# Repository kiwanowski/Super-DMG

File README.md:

# Super-DMG
a consolized Game Boy
## Features
* it has an HDMI port - [based on GbHdmi by Martoni](https://github.com/Martoni/GbHdmi)
* it lets you connect various bluetooth controllers - [based on BlueRetro by darthcloud](https://github.com/darthcloud/BlueRetro)

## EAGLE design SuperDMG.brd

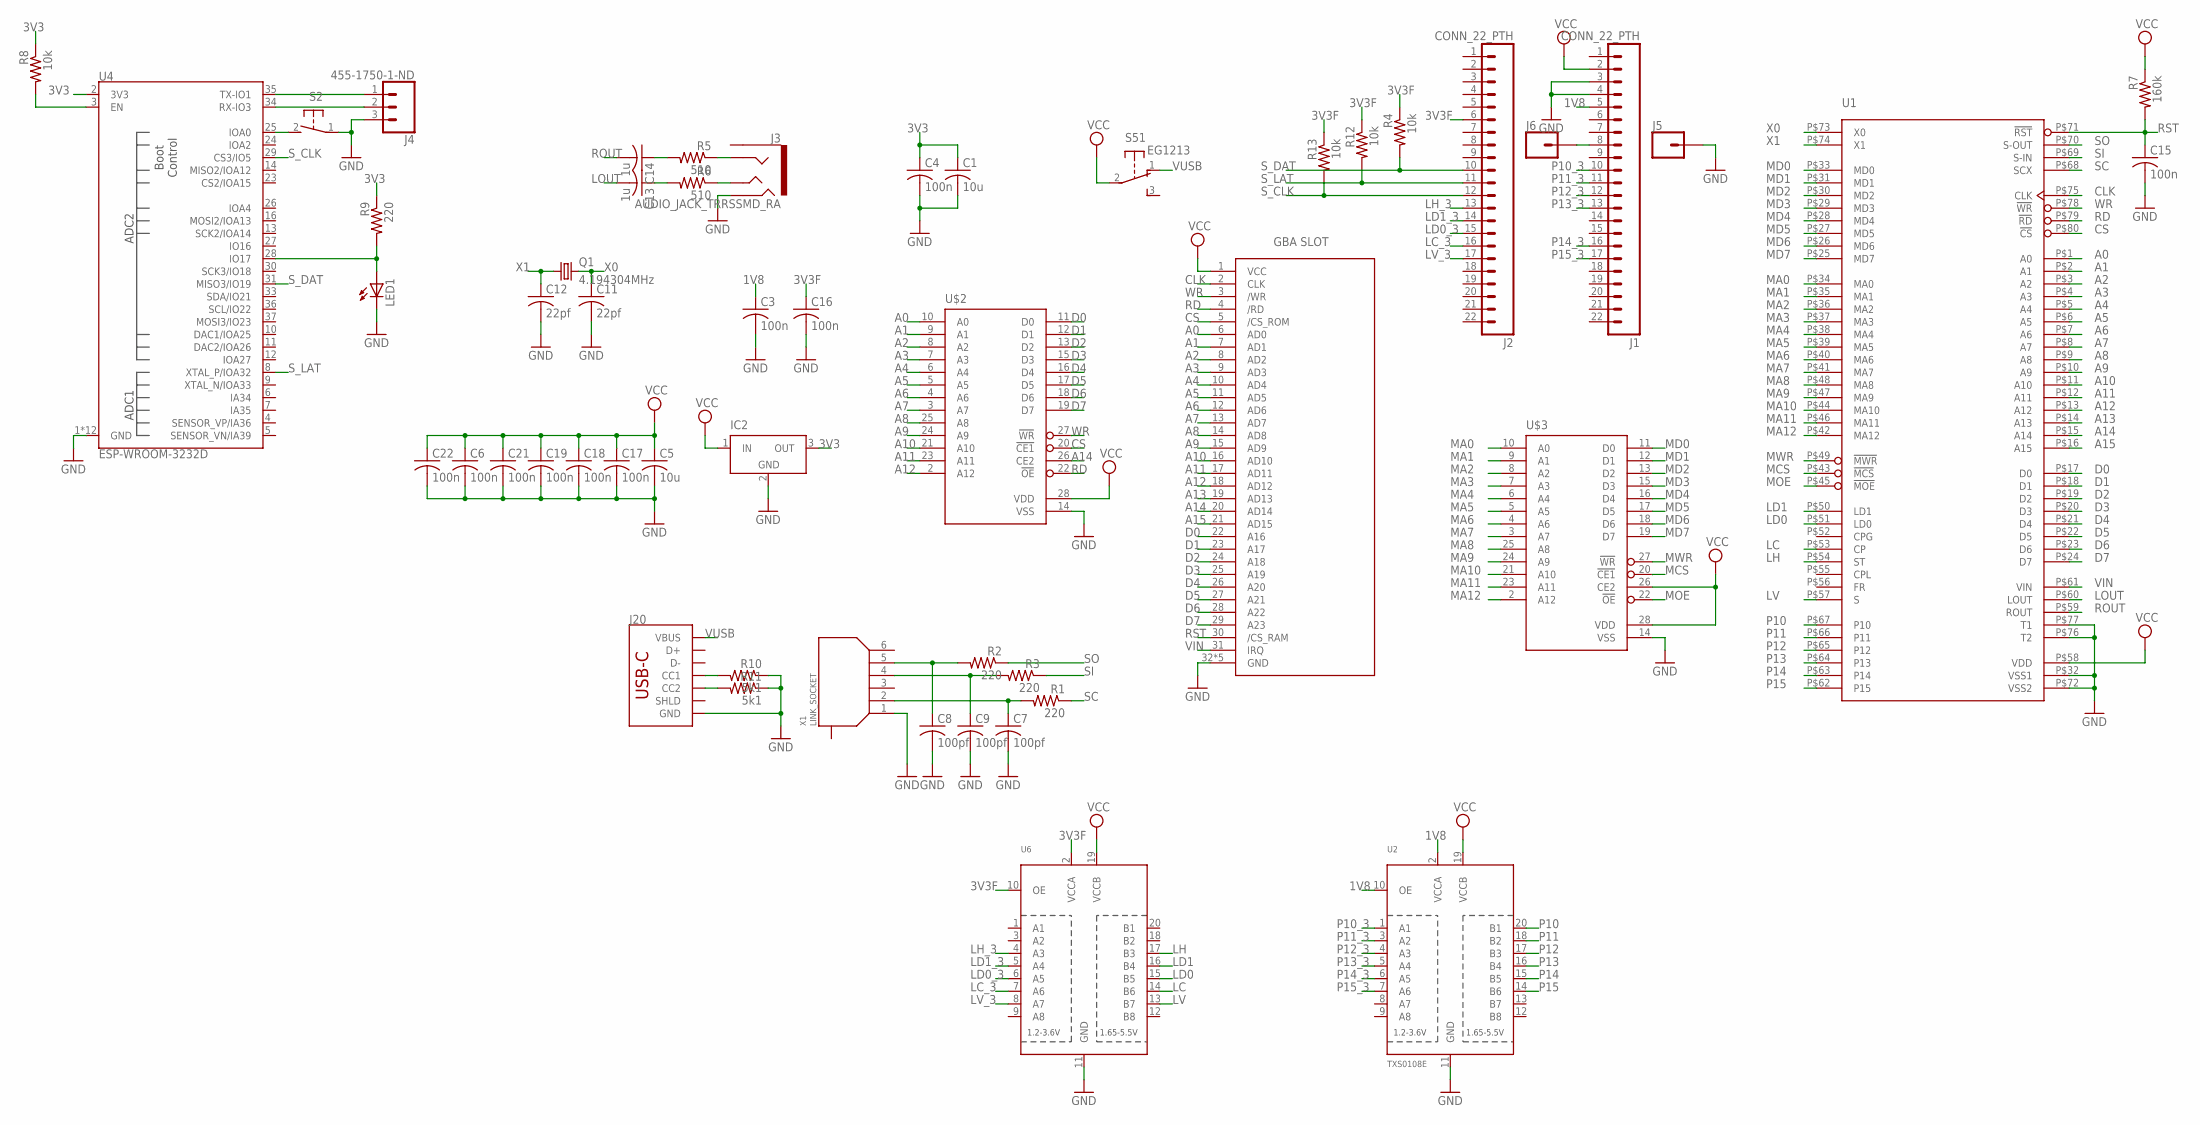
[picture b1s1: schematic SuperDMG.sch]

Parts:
C1, C5: 10u; C0805
C3, C4, C6, C15, C16, C17, C18, C19, C21, C22: 100n; C0805
C7, C8, C9: 100pf; C0805
C11, C12: 22pf; C0805
C13, C14: 1u; C0805
IC2: LT1129CST5; SOT223
J1, J2: CONN_22_PTH; 1X22
J3: AUDIO_JACK_TRRSSMD_RA; AUDIO_JACK_3.5MM_TRRS_SMD_RA
J4: 455-1750-1-ND; 1X03
J5, J6: CONN_01; 1X01
J20: USB_C_2-LAYER_PADS; USB-C-16P-2LAYER-PADS
LED1: LEDCHIP-LED0805; CHIP-LED0805
Q1: 4.194304MHz; HC49U-V
R1, R2, R3, R9: 220; R0805
R4, R8, R12, R13: 10k; R0805
R5, R6: 510; R0805
R7: 160k; R0805
R10, R11: 5k1; R0805
S2: 31-XX; B3F-31XX
S5: EG1213
U1: CPU-1GDMG; CPU-1G
U2: TXS0108E; TSSOP20
U4: ESP-WROOM-3232D; ESP-WROOM-32D
U6: TXB0108PWR; TSSOP20
U$1: GBA-SLOTSMD; GBA-SLOT
U$2, U$3: LH5264; SO28
X1: LINK_SOCKET

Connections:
1V8: C3.1, J1.5, U2.2 (VCCA), U2.10 (OE)
3V3: C1.1, C4.1, IC2.3 (OUT), R8.1, R9.1, U4.2 (3V3)
3V3F: C16.1, J2.6, R4.1, R12.1, R13.1, U6.2 (VCCA), U6.10 (OE)
A0: U1.P$1 (A0), U$1.6 (AD0), U$2.10 (A0)
A1: U1.P$2 (A1), U$1.7 (AD1), U$2.9 (A1)
A2: U1.P$3 (A2), U$1.8 (AD2), U$2.8 (A2)
A3: U1.P$4 (A3), U$1.9 (AD3), U$2.7 (A3)
A4: U1.P$5 (A4), U$1.10 (AD4), U$2.6 (A4)
A5: U1.P$6 (A5), U$1.11 (AD5), U$2.5 (A5)
A6: U1.P$7 (A6), U$1.12 (AD6), U$2.4 (A6)
A7: U1.P$8 (A7), U$1.13 (AD7), U$2.3 (A7)
A8: U1.P$9 (A8), U$1.14 (AD8), U$2.25 (A8)
A9: U1.P$10 (A9), U$1.15 (AD9), U$2.24 (A9)
A10: U1.P$11 (A10), U$1.16 (AD10), U$2.21 (A10)
A11: U1.P$12 (A11), U$1.17 (AD11), U$2.23 (A11)
A12: U1.P$13 (A12), U$1.18 (AD12), U$2.2 (A12)
A13: U1.P$14 (A13), U$1.19 (AD13)
A14: U1.P$15 (A14), U$1.20 (AD14), U$2.26 (CE2)
A15: U1.P$16 (A15), U$1.21 (AD15)
CLK: U1.P$75 (CLK), U$1.2 (CLK)
CS: U1.P$80 (!CS), U$1.5 (/CS_ROM), U$2.20 (!CE1)
D0: U1.P$17 (D0), U$1.22 (A16), U$2.11 (D0)
D1: U1.P$18 (D1), U$1.23 (A17), U$2.12 (D1)
D2: U1.P$19 (D2), U$1.24 (A18), U$2.13 (D2)
D3: U1.P$20 (D3), U$1.25 (A19), U$2.15 (D3)
D4: U1.P$21 (D4), U$1.26 (A20), U$2.16 (D4)
D5: U1.P$22 (D5), U$1.27 (A21), U$2.17 (D5)
D6: U1.P$23 (D6), U$1.28 (A22), U$2.18 (D6)
D7: U1.P$24 (D7), U$1.29 (A23), U$2.19 (D7)
GND: C1.2, C3.2, C4.2, C5.2, C6.2, C7.2, C8.2, C9.2, C11.2, C12.2, C15.2, C16.2, C17.2, C18.2, C19.2, C21.2, C22.2, IC2.2 (GND), IC2.4 (GND), J1.3, J1.4, J3.RING2, J4.3, J5.1, J20.GND, J20.GND2 (GND), LED1.C, R10.1, R11.1, S2.1, U1.P$32 (VSS1), U1.P$72 (VSS2), U1.P$76 (T2), U1.P$77 (T1), U2.11 (GND), U4.1 (GND), U4.15 (GND), U4.38 (GND), U4.GND, U4.GNDT1 (GND), U4.GNDT2 (GND), U4.GNDT3 (GND), U4.GNDT4 (GND), U4.GNDT5 (GND), U4.GNDT6 (GND), U4.GNDT7 (GND), U4.GNDT8 (GND), U6.11 (GND), U$1.32 (GND), U$1.SHIELD_1 (GND), U$1.SHIELD_2 (GND), U$1.SHIELD_3 (GND), U$1.SHIELD_4 (GND), U$2.14 (VSS), U$3.14 (VSS), X1.1
LC: U1.P$53 (CP), U6.14 (B6)
LC_3: J2.16, U6.7 (A6)
LD0: U1.P$51 (LD0), U6.15 (B5)
LD0_3: J2.15, U6.6 (A5)
LD1: U1.P$50 (LD1), U6.16 (B4)
LD1_3: J2.14, U6.5 (A4)
LH: U1.P$54 (ST), U6.17 (B3)
LH_3: J2.13, U6.4 (A3)
LOUT: C13.2, U1.P$60 (LOUT)
LV: U1.P$57 (S), U6.13 (B7)
LV_3: J2.17, U6.8 (A7)
MA0: U1.P$34 (MA0), U$3.10 (A0)
MA1: U1.P$35 (MA1), U$3.9 (A1)
MA2: U1.P$36 (MA2), U$3.8 (A2)
MA3: U1.P$37 (MA3), U$3.7 (A3)
MA4: U1.P$38 (MA4), U$3.6 (A4)
MA5: U1.P$39 (MA5), U$3.5 (A5)
MA6: U1.P$40 (MA6), U$3.4 (A6)
MA7: U1.P$41 (MA7), U$3.3 (A7)
MA8: U1.P$48 (MA8), U$3.25 (A8)
MA9: U1.P$47 (MA9), U$3.24 (A9)
MA10: U1.P$44 (MA10), U$3.21 (A10)
MA11: U1.P$46 (MA11), U$3.23 (A11)
MA12: U1.P$42 (MA12), U$3.2 (A12)
MCS: U1.P$43 (!MCS), U$3.20 (!CE1)
MD0: U1.P$33 (MD0), U$3.11 (D0)
MD1: U1.P$31 (MD1), U$3.12 (D1)
MD2: U1.P$30 (MD2), U$3.13 (D2)
MD3: U1.P$29 (MD3), U$3.15 (D3)
MD4: U1.P$28 (MD4), U$3.16 (D4)
MD5: U1.P$27 (MD5), U$3.17 (D5)
MD6: U1.P$26 (MD6), U$3.18 (D6)
MD7: U1.P$25 (MD7), U$3.19 (D7)
MOE: U1.P$45 (!MOE), U$3.22 (!OE)
MWR: U1.P$49 (!MWR), U$3.27 (!WR)
unnamed: C8.1, R2.2, X1.5
unnamed: C9.1, R3.2, X1.4
unnamed: J1.8, J6.1
unnamed: C7.1, R1.2, X1.2
unnamed: R8.2, U4.3 (EN)
unnamed: LED1.A, R9.2, U4.28 (IO17)
unnamed: J3.RING1, R5.1
unnamed: J20.A5 (CC1), R10.2
unnamed: J20.B5 (CC2), R11.2
unnamed: J3.TIP, R6.1
unnamed: C14.1, R5.2
unnamed: C13.1, R6.2
unnamed: S2.2 (S), U4.25 (IOA0)
P10: U1.P$67 (P10), U2.20 (B1)
P10_3: J1.10, U2.1 (A1)
P11: U1.P$66 (P11), U2.18 (B2)
P11_3: J1.11, U2.3 (A2)
P12: U1.P$65 (P12), U2.17 (B3)
P12_3: J1.12, U2.4 (A3)
P13: U1.P$64 (P13), U2.16 (B4)
P13_3: J1.13, U2.5 (A4)
P14: U1.P$63 (P14), U2.15 (B5)
P14_3: J1.16, U2.6 (A5)
P15: U1.P$62 (P15), U2.14 (B6)
P15_3: J1.17, U2.7 (A6)
RD: U1.P$79 (!RD), U$1.4 (/RD), U$2.22 (!OE)
ROUT: C14.2, U1.P$59 (ROUT)
RST: C15.1, R7.2, U1.P$71 (!RST), U$1.30 (/CS_RAM)
RX: J4.2, U4.34 (RX-IO3)
SC: R1.1, U1.P$68 (SCX)
SI: R3.1, U1.P$69 (S-IN)
SO: R2.1, U1.P$70 (S-OUT)
S_CLK: J2.12, R13.2, U4.29 (CS3/IO5)
S_DAT: J2.10, R4.2, U4.31 (MISO3/IO19)
S_LAT: J2.11, R12.2, U4.8 (XTAL_P/IOA32)
TX: J4.1, U4.35 (TX-IO1)
VCC: C5.1, C6.1, C17.1, C18.1, C19.1, C21.1, C22.1, IC2.1 (IN), J1.2, R7.1, S5.2, U1.P$58 (VDD), U2.19 (VCCB), U6.19 (VCCB), U$1.1 (VCC), U$2.28 (VDD), U$3.26 (CE2), U$3.28 (VDD)
VIN: U1.P$61 (VIN), U$1.31 (IRQ)
VUSB: J20.VBUS1 (VBUS), J20.VBUS2 (VBUS), S5.1 (O)
WR: U1.P$78 (!WR), U$1.3 (/WR), U$2.27 (!WR)
X0: C11.1, Q1.2, U1.P$73 (X0)
X1: C12.1, Q1.1, U1.P$74 (X1)

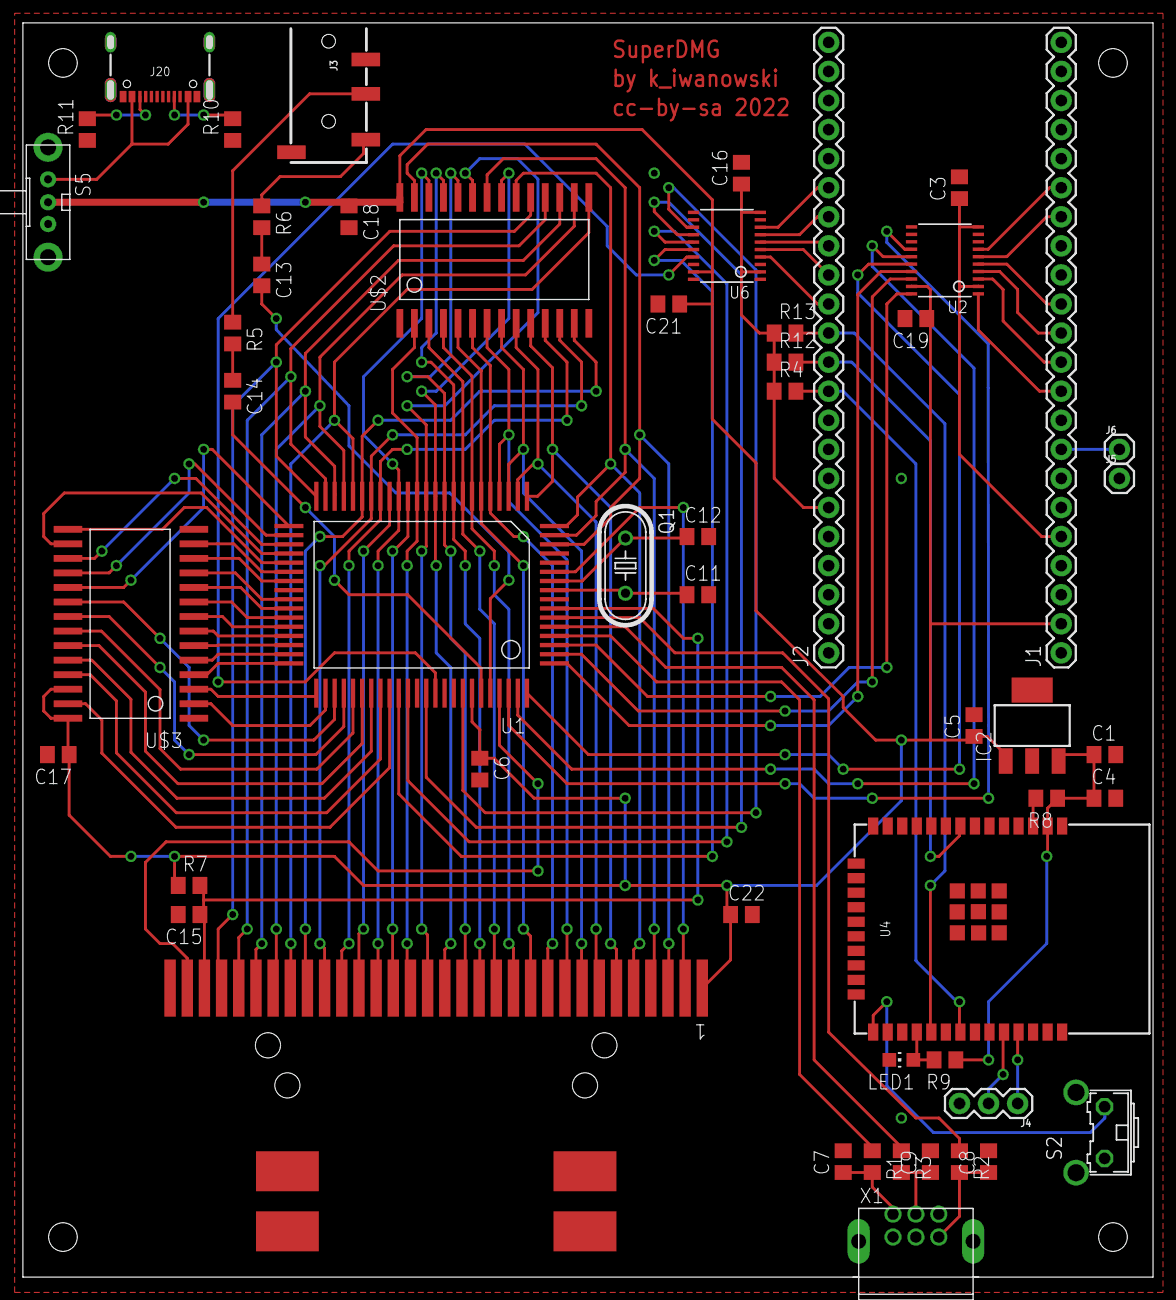
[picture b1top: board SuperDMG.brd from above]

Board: 2 copper layers, 98.1 x 109.0 mm, 52 parts (0 on the bottom side), 107 nets.

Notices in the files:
SuperDMG.brd:
cc-by-sa 2022
parts and their libraries:
lbr_SparkFun-Eagle-Libraries_SparkFun-Co: Licensing: Creative Commons ShareAlike 4.0 International - https://creativecommons.org/licenses/by-sa/4.0
